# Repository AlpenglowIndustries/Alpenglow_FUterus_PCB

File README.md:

# Alpenglow_FUterus_PCB

This is how I feel about legislating women's bodies.  

Thanks to [Claire Danielle Cassidy](https://linktr.ee/ClaireDanielleCassidy) for giving me the urge to make a board, while helping her make a board!  I did the uterus artwork a while back and then the design languished for several years.  I picked it back up and made it into a through-hole soldering kit.  The idea is to use 3x 5mm candle-flicker red LEDs on the back, the uterus is bare FR-4 on both sides, so it will light up red.  Powered by a coin cell and uses one resistor to mildly limit current through all 3 LEDs.  Excellent write-up here by EMSL about resistors vs no resistors on coin-cell-powered LED throwies/badges.
https://www.evilmadscientist.com/2009/some-thoughts-on-throwies/

I was going to route this board normally, but then thought about how cool [Chipperdoodles'](https://chippydootles.com/docs/anwaar/anwaar-families/) boards are, all hand-drawn traces.  Why not fuck around with this?  And why not just scribble the fuckers?  Madness ensued.  Me and [Architeuthis Flux](https://docs.jumperless.org/#find-me-on-the-internet) figured out that if the squiggles were polygons, I could easily add a net to them without needing any schematic symbol.  I used ProCreate on my iPad to draw the circuit over a screenshot of the layout, and unfortunately it only exports as raster graphics, jpeg or png.  I could use KiCad's built-in Image Converter to import them to a footprint.  Then moved them to a User layer.  Place them in the PCB which automatically makes them a "footprint" there is no avoiding this even if you copy/paste the polygon from footprint editor it will still place in the PCB editor as a footprint, plot the user layer as an svg, then re-import the svg as a graphic.  Voila!  100% KiCad chain of raster to svg to polygon.  There was a little bit of scaling to figure out, but I could import all the squiggly traces as one graphic (a bunch of polygons automatically grouped), place them over the pads on the PCB, and all traces were automatically assigned the right nets.  It was wild, I can't believe PCB software has come this far.  Now that they were all assigned nets, I could actually run a DRC on the board.  I recommend turning some things to "ignore" under "Violation Severity" in Design Rule settings: footprint has no courtyard defined, silkscreen clipped by soldermask, silkscreen clipped by board edge, footprint doesn't match copy in library (in case you decide to keep silk-only art as footprints since you don't need to attach a net to it, and then need to re-size it).  DRC will take a while.  Save first in case it crashes.

I had a weird error pop up when using Fabrication Toolkit to export a Gerber package for JLC - Footprint.Duplicate() missing 1 required positional argument: 'addToParentGroup'.  It was an issue with the actual normal component footprints, not any of the silk art that I had set to DNP and Exclude from BOM.  I couldn't figure out what the issue was, and since this was just a PCB fab job without an assembly component, I just set all footprints to DNP.  Not sure if this is a KiCad 10 issue, I just upgraded and 10 is only a few days old, so there are probably some kinks to work out.

Note that in this design, all traces are unmasked for decorative purposes.  This means it's hella easy to short this board out.  Coin cells are pretty cool with that, but just an FYI especially for beginning solderers, be careful about accidentally bridging traces/pad at the top LED pads.  Short and long legs of the LEDs and +/- are noted on the board.

This started off as this surface mount design:

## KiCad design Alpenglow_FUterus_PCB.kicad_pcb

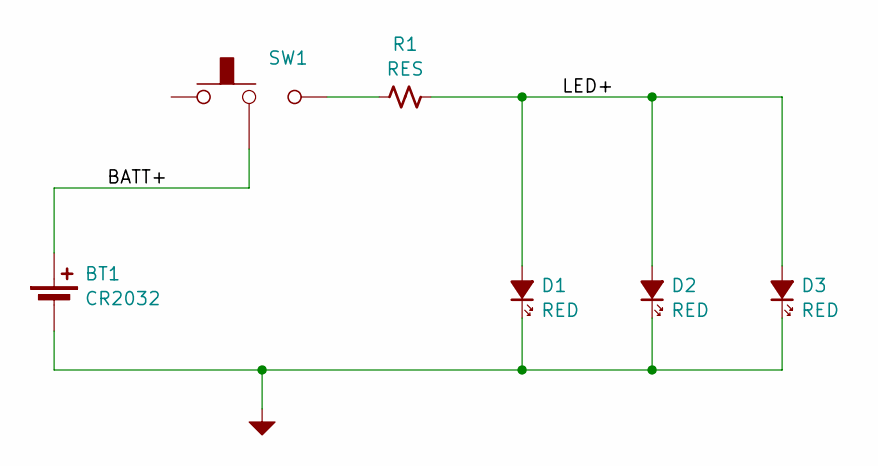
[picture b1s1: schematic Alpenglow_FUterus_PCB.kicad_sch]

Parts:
BT1: CR2032; CR2032_Holder_Clip_Through_Hole-BS-03-A1AJ001
D1, D2, D3: RED; LED_D5.0mm_Horizontal_O3.81mm_Z3.0mm
R1: RES; R_Axial_DIN0207_L6.3mm_D2.5mm_P10.16mm_Horizontal
SW1: SW_SLIDE; SW_SPDT_SLIDE_THRU_RTA

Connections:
/BATT+: BT1.1 (+), SW1.2
/LED+: D1.2 (A), D2.2 (A), D3.2 (A), R1.2
GND: BT1.2 (-), D1.1 (K), D2.1 (K), D3.1 (K)
unnamed: R1.1, SW1.3

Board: 2 copper layers, 11 parts (6 on the bottom side), 4 nets, no tracks yet.

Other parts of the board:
G1: UterusSoldermask; VagArmsSM
G2: FUCK
G3: OFF!
G4: aka the Boobterus
G5: The FUterus by Carrie Sundra

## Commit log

2024-07-01 Update README.md
    updated description
2024-07-01 initial commit of files
2024-07-02 Added easyeda library and LED side mount pattern, updated PCB, aligned uterus copper & mask
2024-07-02 deleted old alternate graphics
2024-07-02 added autosaved files temporary file to gitignore
2024-07-02 fixed typo
2024-07-02 still a WIP, working on main component placement, considering processor vs self-blinking LEDs
2026-03-21 picked it back up and started changes for through-hole kit
2026-03-22 artwork progress, still needs cleanup
2026-03-22 tweaks, removed corrupted Squiggles footprint
2026-03-22 Re-made Squiggles component, removed extras from PCB, fixed center LED+ squiggle so it's not close to GND pads
2026-03-22 silk component text tweaks
2026-03-22 on/off symbols added
2026-03-22 updated battery holder for text fields
2026-03-22 Organized artwork into folder, linked all text to actual footprints in libraries
2026-03-22 Cleaned up, added text, set components to DNP to avoid Fab Toolkit error, sent to JLC
2026-03-22 added info on the PCB to the readme
2026-03-22 Update README.md
    added pix and links
